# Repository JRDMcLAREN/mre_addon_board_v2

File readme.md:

# mre_addon_board_v2

Addon board for microrusEFI ECU.
Wideband controller wiring is based on https://github.com/mck1117/wideband, official rusEFI wideband controller.
This is a version using STM32F072C8Tx or STM32F072CBTx MCU in LQFP48 package.
(STM32F042C6T6 is not recommended for future release)

This addon board has build-in rusEFI wideband controller, microSD card slot and K-Thermocouple controller.
It can be used on all MREs with appropriate connector headers.

Wideband controller requires:
* CAN bus connectivity 
* additional power supply from 12V_MREL pin for sensor heater.
(not required for "my" MRE versions - R0.5.5rc, R0.6.1rc)

~~LSU 4.9 sensor wires are connected via MOLEX MicroFit 3x2 connector 43045-0601 or 43045-0612
K-Thermocouple wires are connected via MOLEX MicroFit 2x1 connector 43045-0202 or 43045-0212~~

Latest version use 2x4 pin connector MOLEX 43045-0800 or 43045-0812 (6pins for LSU and 2pins for K-Thermocouple).

Two analog outputs for external gauages are in progress.

SPI ChipSelect CS# pins:
PA15 - for EGT chip
PB9 - for microSD card

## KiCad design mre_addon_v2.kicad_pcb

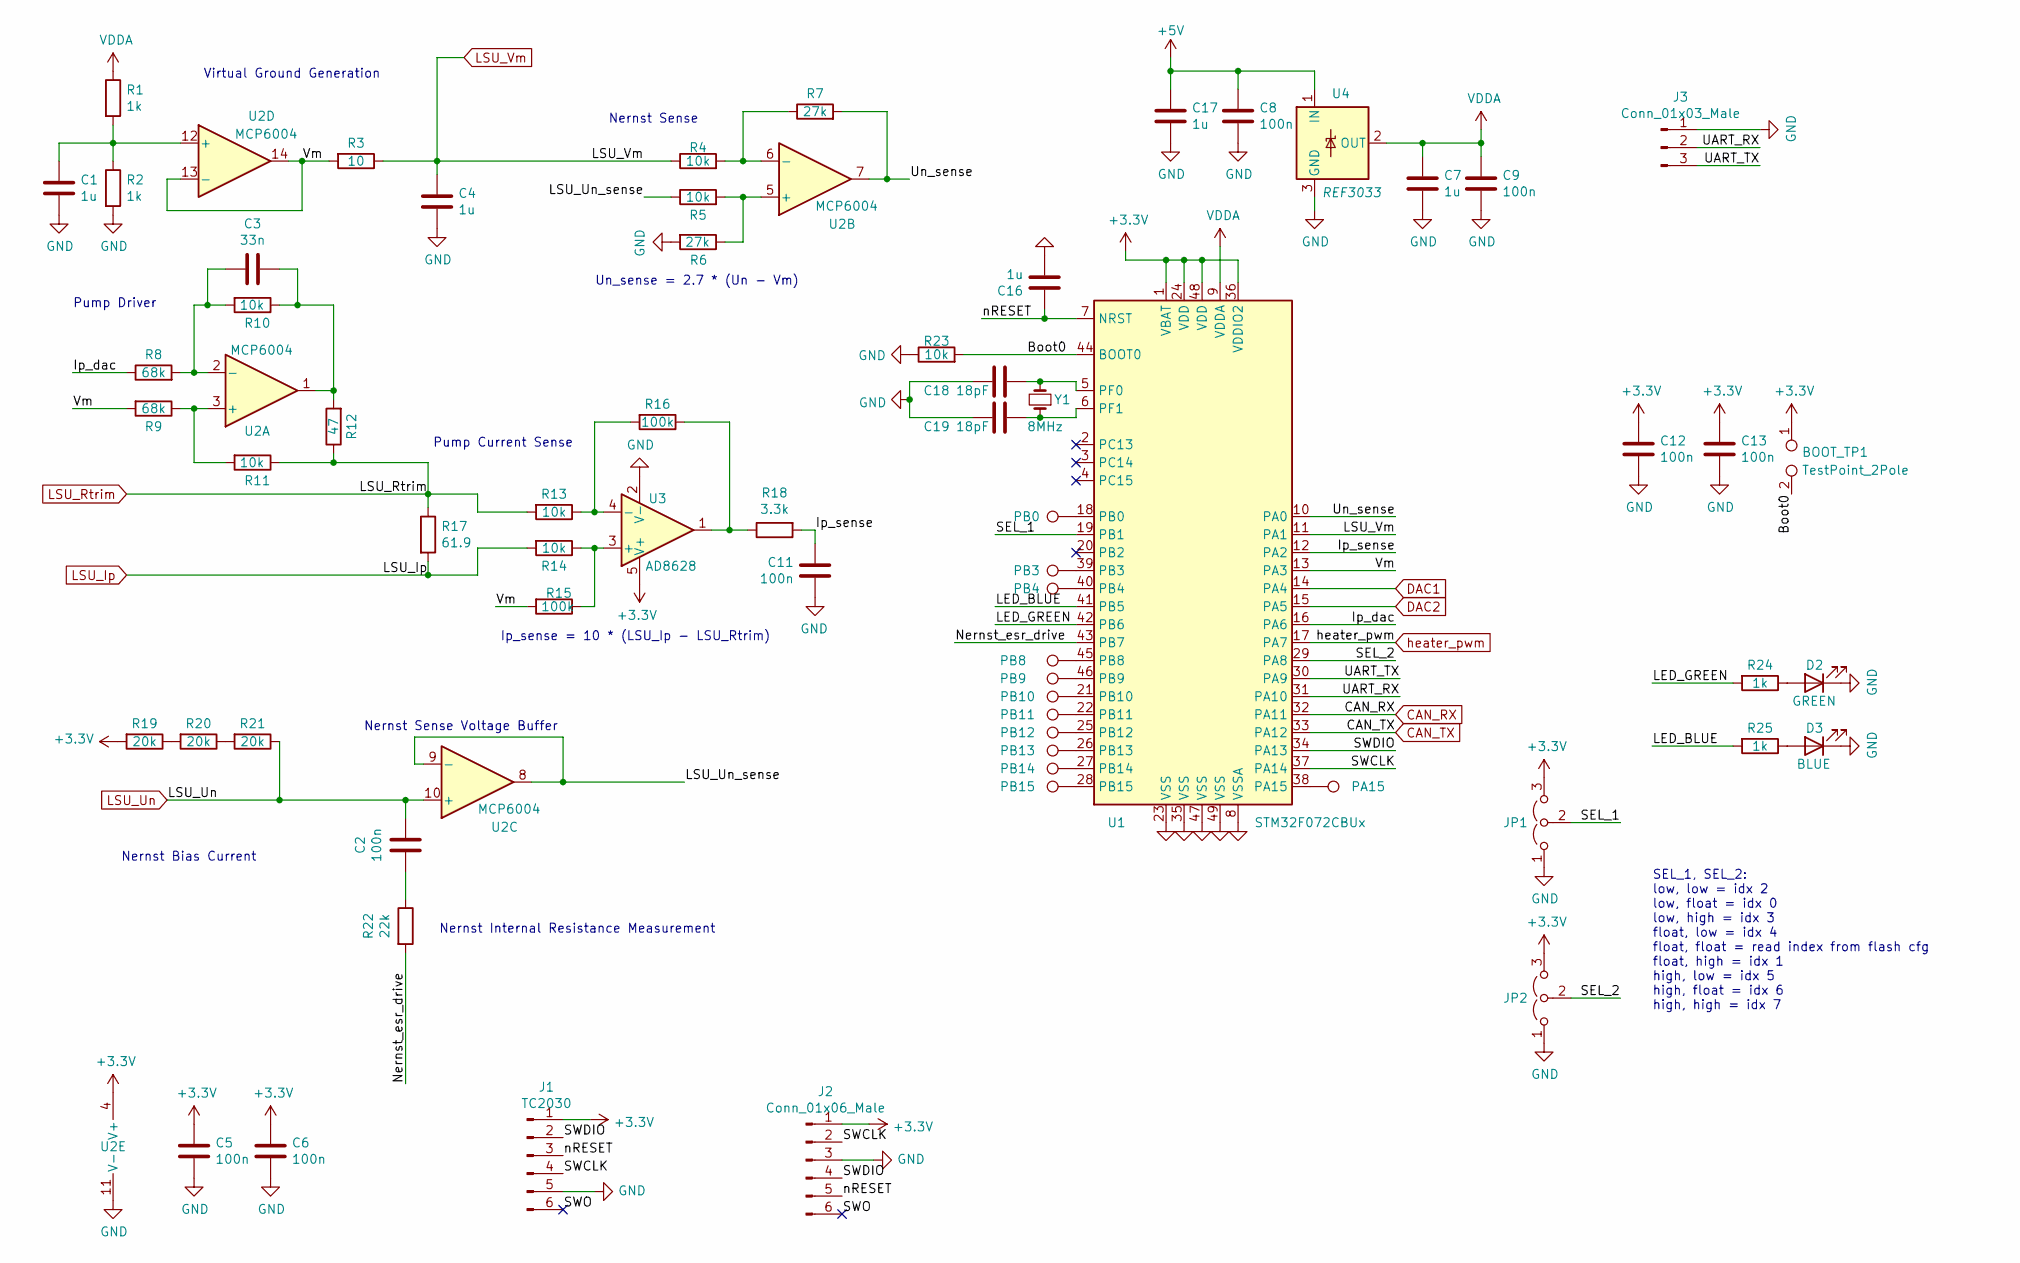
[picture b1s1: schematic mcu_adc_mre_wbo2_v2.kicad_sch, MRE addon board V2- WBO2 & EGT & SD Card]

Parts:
BOOT_TP1: TestPoint_2Pole; TestPoint_Bridge_Pitch2.54mm_Drill0.7mm
C1, C4, C7, C16, C17: 1u; C_0603_1608Metric; LCSC C52923
C2, C5, C6, C9, C11, C12, C13: 100n; C_0603_1608Metric; LCSC C1525
C3: 33n; C_0603_1608Metric; LCSC C1585
C8: 100n; C_0603_1608Metric
C18, C19: 18pF; C_0603_1608Metric
D2: GREEN; LED_0603_1608Metric; LCSC C72043
D3: BLUE; LED_0603_1608Metric; LCSC C72041
J1: TC2030; Tag-Connect_TC2030-IDC-NL_2x03_P1.27mm_Vertical
J2: Conn_01x06_Male; PinHeader_1x06_P2.54mm_Vertical
J3: Conn_01x03_Male; PinHeader_1x03_P2.54mm_Vertical
JP1, JP2: Jumper_3_Open; SolderJumper-3_P1.3mm_Open_Pad1.0x1.5mm
PA15: TestPoint; TestPoint_Pad_D1.0mm
PB0, PB3, PB4, PB8, PB9, PB10, PB11, PB12, PB13, PB14, PB15: TestPoint; TestPoint_Pad_D1.0mm
R1, R2, R24, R25: 1k; R_0603_1608Metric; LCSC C11702
R3: 10; R_0603_1608Metric; LCSC C25077
R4, R5, R10, R11, R13, R14, R23: 10k; R_0603_1608Metric; LCSC C25744
R6, R7: 27k; R_0603_1608Metric; LCSC C25771
R8, R9: 68k; R_0603_1608Metric; LCSC C36871
R12: 47; R_0603_1608Metric; LCSC C25118
R15, R16: 100k; R_0603_1608Metric; LCSC C25741
R17: 61.9; R_0603_1608Metric; LCSC C23092
R18: 3.3k; R_0603_1608Metric; LCSC C25890
R19, R20, R21: 20k; R_0603_1608Metric; LCSC C25765
R22: 22k; R_0603_1608Metric; LCSC C25768
U1: STM32F072CBUx; LQFP-48_7x7mm_P0.5mm
U2: MCP6004; TSSOP-14_4.4x5mm_P0.65mm; LCSC C50282
U3: AD8628; TSOT-23-5; LCSC C29309
U4: REF3033; SOT-23; LCSC C36658
Y1: 8MHz; Crystal_SMD_5032-2Pin_5.0x3.2mm

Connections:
+3.3V: BOOT_TP1.1, C5.1, C6.1, C12.1, C13.1, J1.1, J2.1, JP1.3 (B), JP2.3 (B), R19.2, U1.1 (VBAT), U1.24 (VDD), U1.36 (VDDIO2), U1.48 (VDD), U2.4 (V+), U3.5 (V+); also elsewhere on the board
+5V: C8.1, C17.1, U4.1 (IN); also elsewhere on the board
/mcu_adc_mre_wbo2_v2/Boot0: BOOT_TP1.2, R23.2, U1.44 (BOOT0)
/mcu_adc_mre_wbo2_v2/Ip_dac: R8.1, U1.16 (PA6)
/mcu_adc_mre_wbo2_v2/Ip_sense: C11.1, R18.2, U1.12 (PA2)
/mcu_adc_mre_wbo2_v2/LED_BLUE: R25.2, U1.41 (PB5)
/mcu_adc_mre_wbo2_v2/LED_GREEN: R24.2, U1.42 (PB6)
/mcu_adc_mre_wbo2_v2/LSU_Un_sense: R5.1, U2.8, U2.9 (-)
/mcu_adc_mre_wbo2_v2/Nernst_esr_drive: R22.2, U1.43 (PB7)
/mcu_adc_mre_wbo2_v2/SEL_1: JP1.2 (C), U1.19 (PB1)
/mcu_adc_mre_wbo2_v2/SEL_2: JP2.2 (C), U1.29 (PA8)
/mcu_adc_mre_wbo2_v2/SWCLK: J1.4, J2.2, U1.37 (PA14); also elsewhere on the board
/mcu_adc_mre_wbo2_v2/SWDIO: J1.2, J2.4, U1.34 (PA13); also elsewhere on the board
/mcu_adc_mre_wbo2_v2/SWO: J1.6, J2.6; also elsewhere on the board
/mcu_adc_mre_wbo2_v2/UART_RX: J3.2, U1.31 (PA10)
/mcu_adc_mre_wbo2_v2/UART_TX: J3.3, U1.30 (PA9)
/mcu_adc_mre_wbo2_v2/Un_sense: R7.2, U1.10 (PA0), U2.7
/mcu_adc_mre_wbo2_v2/Vm: R3.2, R9.2, R15.2, U1.13 (PA3), U2.13 (-), U2.14
/mcu_adc_mre_wbo2_v2/nRESET: C16.1, J1.3, J2.5, U1.7 (NRST); also elsewhere on the board
CAN_RX: U1.32 (PA11); also elsewhere on the board
CAN_TX: U1.33 (PA12); also elsewhere on the board
DAC1: U1.14 (PA4); also elsewhere on the board
DAC2: U1.15 (PA5); also elsewhere on the board
GND: C1.2, C4.2, C5.2, C6.2, C7.2, C8.2, C9.2, C11.2, C12.2, C13.2, C16.2, C17.2, C18.1, C19.1, D2.1 (K), D3.1 (K), J1.5, J2.3, J3.1, JP1.1 (A), JP2.1 (A), R2.2, R6.2, R23.1, U1.8 (VSSA), U1.23 (VSS), U1.35 (VSS), U1.47 (VSS), U1.49 (VSS), U2.11 (V-), U3.2 (V-), U4.3 (GND); also elsewhere on the board
LSU_Ip: R14.2, R17.2; also elsewhere on the board
LSU_Rtrim: R11.1, R12.1, R13.2, R17.1; also elsewhere on the board
LSU_Un: C2.1, R21.1, U2.10 (+); also elsewhere on the board
LSU_Vm: C4.1, R3.1, R4.1, U1.11 (PA1); also elsewhere on the board
unnamed: C1.1, R1.2, R2.1, U2.12 (+)
unnamed: C2.2, R22.1
unnamed: C3.1, R10.1, R12.2, U2.1
unnamed: C3.2, R8.2, R10.2, U2.2 (-)
unnamed: C18.2, U1.5 (PF0), Y1.2
unnamed: C19.2, U1.6 (PF1), Y1.1
unnamed 54: D2.2 (A), R24.1; also elsewhere on the board
unnamed 55: D3.2 (A), R25.1; also elsewhere on the board
unnamed: PA15.1, U1.38 (PA15)
unnamed: PB0.1, U1.18 (PB0)
unnamed: PB3.1, U1.39 (PB3)
unnamed: PB4.1, U1.40 (PB4)
unnamed: PB8.1, U1.45 (PB8)
unnamed: PB9.1, U1.46 (PB9)
unnamed: PB10.1, U1.21 (PB10)
unnamed: PB11.1, U1.22 (PB11)
unnamed: PB12.1, U1.25 (PB12)
unnamed: PB13.1, U1.26 (PB13)
unnamed: PB14.1, U1.27 (PB14)
unnamed: PB15.1, U1.28 (PB15)
unnamed: R4.2, R7.1, U2.6 (-)
unnamed: R5.2, R6.1, U2.5 (+)
unnamed: R9.1, R11.2, U2.3 (+)
unnamed 72: R13.1, R16.2, U3.4 (-); also elsewhere on the board
unnamed 73: R14.1, R15.1, U3.3 (+); also elsewhere on the board
unnamed 74: R16.1, R18.1, U3.1; also elsewhere on the board
unnamed: R19.1, R20.2
unnamed: R20.1, R21.2
VDDA: C7.1, C9.1, R1.1, U1.9 (VDDA), U4.2 (OUT)
heater_pwm: U1.17 (PA7); also elsewhere on the board

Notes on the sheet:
Un_sense = 2.7 * (Un - Vm)
Virtual Ground Generation
Pump Current Sense
Pump Driver
Ip_sense = 10 * (LSU_Ip - LSU_Rtrim)
Nernst Sense
Nernst Internal Resistance Measurement
Nernst Sense Voltage Buffer
SEL_1, SEL_2: low, low = idx 2 low, float = idx 0 low, high = idx 3 float, low = idx 4 float, float = read index from flash cfg float, high = idx 1 high, low = idx 5 high, float = idx 6 high, high = idx 7
Nernst Bias Current

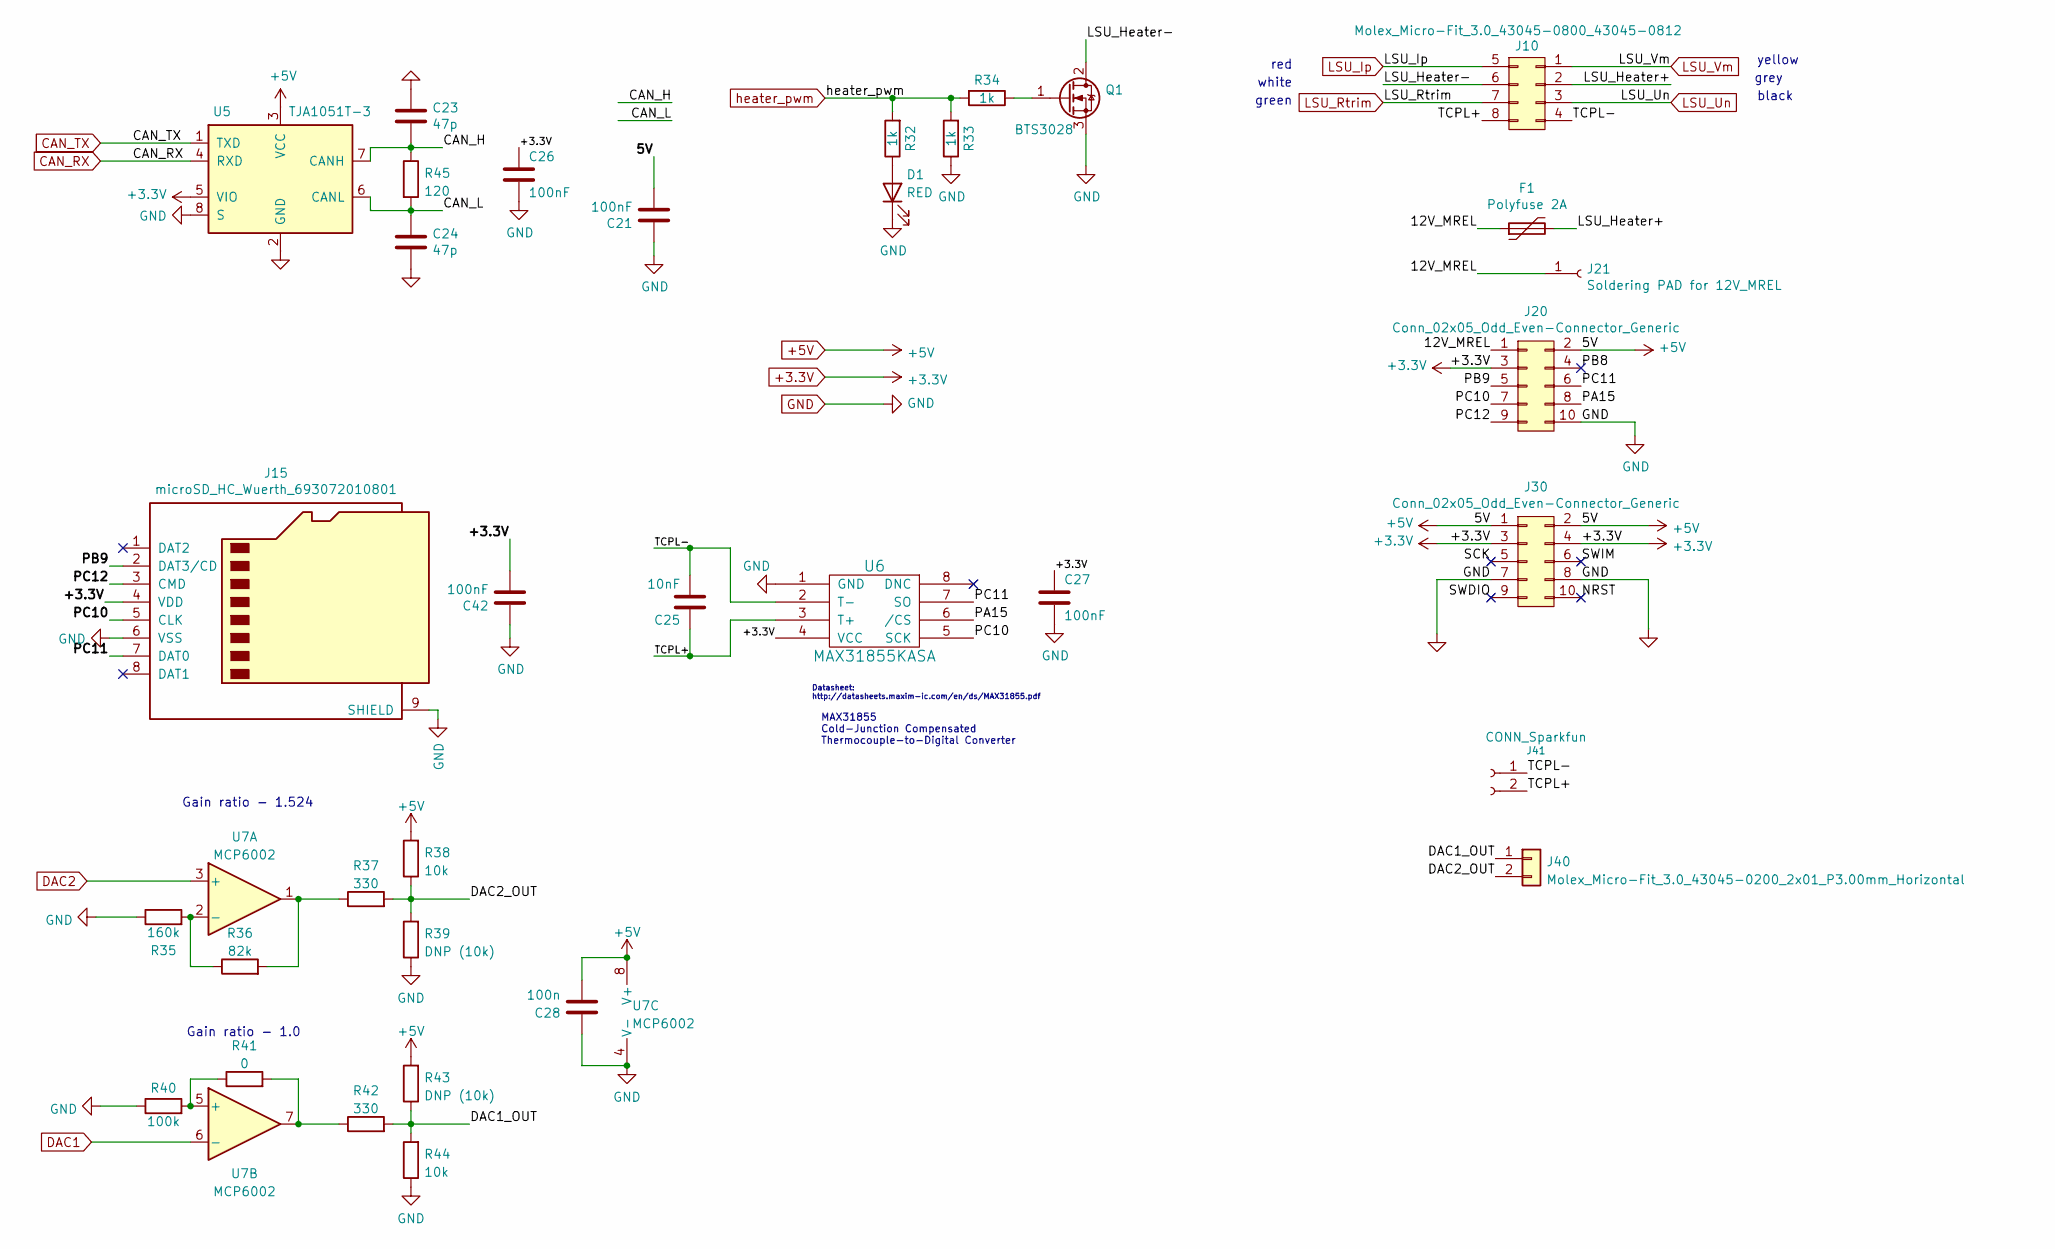
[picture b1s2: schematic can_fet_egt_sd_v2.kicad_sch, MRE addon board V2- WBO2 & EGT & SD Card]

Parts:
C21, C42: 100nF; C_0603_1608Metric; Part # C0603C104J5RACTU; LCSC C14663
C23, C24: 47p; C_0603_1608Metric; LCSC C1567
C25: 10nF; C_0603_1608Metric
C26, C27: 100nF; C_0603_1608Metric
C28: 100n; C_0603_1608Metric
D1: RED; LED_0603_1608Metric; LCSC C2286
F1: Polyfuse 2A; R_2816_7142Metric
J10: Molex_Micro-Fit_3.0_43045-0800_43045-0812; Molex_Micro-Fit_3.0_43045-0800_2x04_P3.00mm_Horizontal
J15: microSD_HC_Wuerth_693072010801; LCSC N/A
J20, J30: Conn_02x05_Odd_Even-Connector_Generic; PinHeader_2x05_P2.54mm_Vertical_SMD
J21: Soldering PAD for 12V_MREL; PinHeader_1x01_P2.54mm_Vertical
J40: Molex_Micro-Fit_3.0_43045-0200_2x01_P3.00mm_Horiz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; Molex_Micro-Fit_3.0_43045-0200_2x01_P3.00mm_Horizontal
J41: CONN_Sparkfun; tcpl_PCC-SMP
Q1: BTS3028; TO-252-2; LCSC C112639
R32, R33, R34: 1k; R_0603_1608Metric; LCSC C11702
R35: 160k; R_0603_1608Metric
R36: 82k; R_0603_1608Metric
R37, R42: 330; R_0603_1608Metric
R38, R44: 10k; R_0603_1608Metric
R39, R43: DNP (10k); R_0603_1608Metric
R40: 100k; R_0603_1608Metric
R41: 0; R_0603_1608Metric
R45: 120; R_0805_2012Metric
U5: TJA1051T-3; SOIC-8_3.9x4.9mm_P1.27mm; LCSC C38695
U6: MAX31855KASA; SOIC-8_3.9x4.9mm_P1.27mm
U7: MCP6002; SOIC-8_3.9x4.9mm_P1.27mm

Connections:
+3.3V: C26.1, C27.1, C42.2, J15.4 (VDD), J20.3, J30.3, J30.4, U5.5 (VIO), U6.4 (VCC); also elsewhere on the board
+5V: C21.2, C28.2, J20.2, J30.1, J30.2, R38.2, R43.2, U5.3 (VCC), U7.8 (V+); also elsewhere on the board
/can_fet_egt_sd_v2/12V_MREL: F1.1, J20.1, J21.1; also elsewhere on the board
/can_fet_egt_sd_v2/CAN_H: C23.2, R45.1, U5.7 (CANH); also elsewhere on the board
/can_fet_egt_sd_v2/CAN_L: C24.1, R45.2, U5.6 (CANL); also elsewhere on the board
/can_fet_egt_sd_v2/DAC1_OUT: J40.1, R42.2, R43.1, R44.2; also elsewhere on the board
/can_fet_egt_sd_v2/DAC2_OUT: J40.2, R37.2, R38.1, R39.2; also elsewhere on the board
/can_fet_egt_sd_v2/LSU_Heater+: F1.2, J10.2; also elsewhere on the board
/can_fet_egt_sd_v2/LSU_Heater-: J10.6, Q1.2 (D); also elsewhere on the board
/can_fet_egt_sd_v2/NRST: J30.10; also elsewhere on the board
/can_fet_egt_sd_v2/PA15: J20.8, U6.6 (/CS); also elsewhere on the board
/can_fet_egt_sd_v2/PB8: J20.4; also elsewhere on the board
/can_fet_egt_sd_v2/PB9: J15.2 (DAT3/CD), J20.5; also elsewhere on the board
/can_fet_egt_sd_v2/PC10: J15.5 (CLK), J20.7, U6.5 (SCK); also elsewhere on the board
/can_fet_egt_sd_v2/PC11: J15.7 (DAT0), J20.6, U6.7 (SO); also elsewhere on the board
/can_fet_egt_sd_v2/PC12: J15.3 (CMD), J20.9; also elsewhere on the board
/can_fet_egt_sd_v2/SCK: J30.5; also elsewhere on the board
/can_fet_egt_sd_v2/SWDIO: J30.9; also elsewhere on the board
/can_fet_egt_sd_v2/SWIM: J30.6; also elsewhere on the board
/can_fet_egt_sd_v2/TCPL+: C25.1, J10.8, J41.2, U6.3 (T+); also elsewhere on the board
/can_fet_egt_sd_v2/TCPL-: C25.2, J10.4, J41.1, U6.2 (T-); also elsewhere on the board
CAN_RX: U5.4 (RXD); also elsewhere on the board
CAN_TX: U5.1 (TXD); also elsewhere on the board
DAC1: U7.6 (-); also elsewhere on the board
DAC2: U7.3 (+); also elsewhere on the board
GND: C21.1, C23.1, C24.2, C26.2, C27.2, C28.1, C42.1, D1.1 (K), J15.6 (VSS), J15.9 (SHIELD), J20.10, J30.7, J30.8, Q1.3 (S), R33.1, R35.1, R39.1, R40.1, R44.1, U5.2 (GND), U5.8 (S), U6.1 (GND), U7.4 (V-); also elsewhere on the board
LSU_Ip: J10.5; also elsewhere on the board
LSU_Rtrim: J10.7; also elsewhere on the board
LSU_Un: J10.3; also elsewhere on the board
LSU_Vm: J10.1; also elsewhere on the board
unnamed 53: D1.2 (A), R32.1; also elsewhere on the board
unnamed: Q1.1 (G), R34.1
unnamed: R35.2, R36.1, U7.2 (-)
unnamed: R36.2, R37.1, U7.1
unnamed: R40.2, R41.1, U7.5 (+)
unnamed: R41.2, R42.1, U7.7
heater_pwm: R32.2, R33.2, R34.2; also elsewhere on the board

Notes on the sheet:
MAX31855 Cold-Junction Compensated Thermocouple-to-Digital Converter
white
Gain ratio - 1.524
Gain ratio - 1.0
green
grey
red
black
Datasheet: http://datasheets.maxim-ic.com/en/ds/MAX31855.pdf
yellow

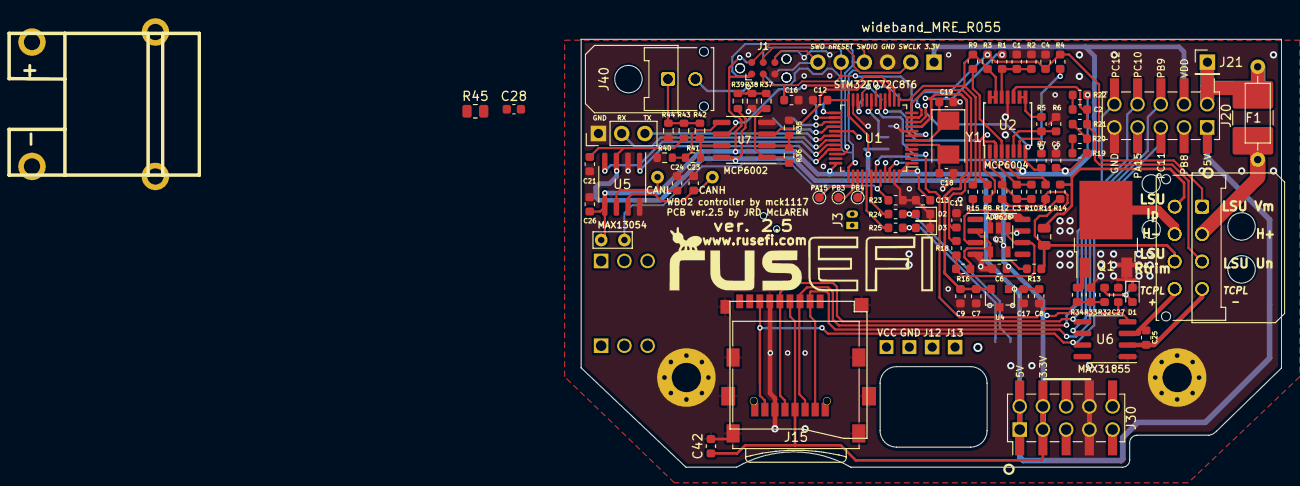
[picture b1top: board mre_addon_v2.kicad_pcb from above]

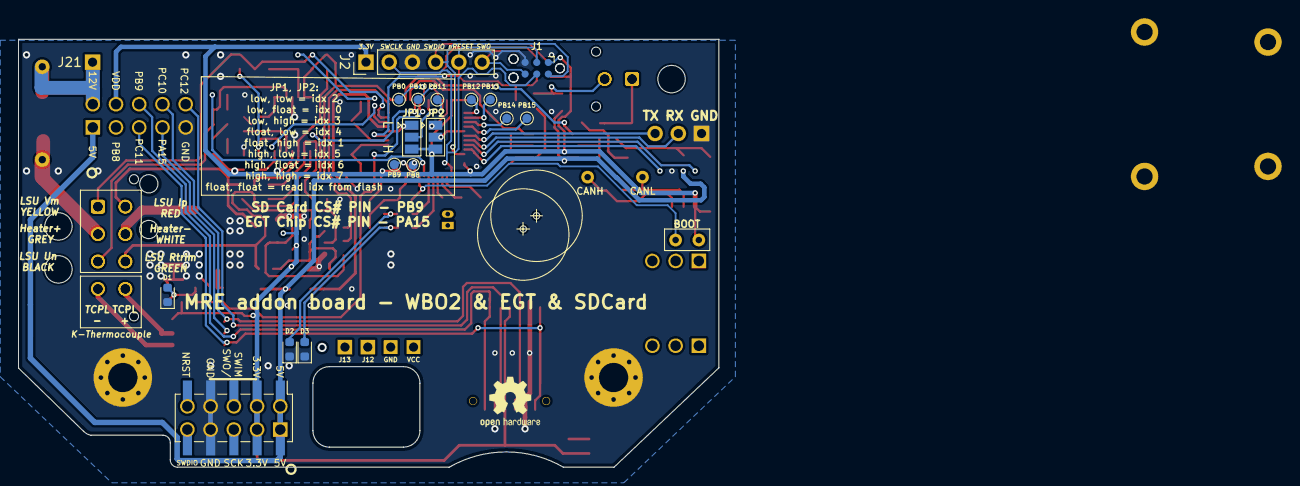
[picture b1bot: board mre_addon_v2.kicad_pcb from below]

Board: 2 copper layers, 76.6 x 46.8 mm, 116 parts (19 on the bottom side), 83 nets.

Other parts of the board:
D1#2: RED; LED_0603_1608Metric
D2#2: GREEN; LED_0603_1608Metric
D3#2: BLUE; LED_0603_1608Metric
F1#2: Polyfuse 2A; R_Axial_DIN0207_L6.3mm_D2.5mm_P10.16mm_Horizontal
G1: LOGO; mre_logo
H1, H2: MountingHole_3.2mm_M3_Pad_Via
J1#2: TC2030; Tag-Connect_TC2030-IDC-NL_2x03_P1.27mm_Vertical
J10#2: Molex_Micro-Fit_3.0_43045-0800_43045-0812; Molex_Micro-Fit_3.0_43045-0812_2x04_P3.00mm_Vertical
J15x: MICRO-SDCARD-CONNECTOR-3300060P1
J30x: Conn_02x05_Odd_Even-Connector_Generic; PinHeader_2x05_P2.54mm_Vertical_SMD
J40#2: Molex_Micro-Fit_3.0_43045-0200_2x01_P3.00mm_Horiz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; Molex_Micro-Fit_3.0_43045-0200_2x01_P3.00mm_Horizontal
LOGO1: DNP; OSHW-Logo2_7.3x6mm_SilkScreen
U0: wideband_MRE_R055
U3x: SO-8_3.9x4.9mm_P1.27mm

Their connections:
+3.3V: J1#2.1, J15x.4, J30x.3, J30x.4, U0.J203, U0.J204, U0.J804, U3x.7; also elsewhere on the board
+5V: J30x.1, J30x.2, U0.J201, U0.J202, U0.J801; also elsewhere on the board
/can_fet_egt_sd_v2/12V_MREL: F1#2.1, U0.J802; also elsewhere on the board
/can_fet_egt_sd_v2/CAN_H: U0.J49; also elsewhere on the board
/can_fet_egt_sd_v2/CAN_L: U0.J50; also elsewhere on the board
/can_fet_egt_sd_v2/DAC1_OUT: J40#2.1; also elsewhere on the board
/can_fet_egt_sd_v2/DAC2_OUT: J40#2.2; also elsewhere on the board
/can_fet_egt_sd_v2/LSU_Heater+: F1#2.2, J10#2.2; also elsewhere on the board
/can_fet_egt_sd_v2/LSU_Heater-: J10#2.6; also elsewhere on the board
/can_fet_egt_sd_v2/NRST: J30x.9, U0.J210; also elsewhere on the board
/can_fet_egt_sd_v2/PA15: U0.J807; also elsewhere on the board
/can_fet_egt_sd_v2/PB8: U0.J803; also elsewhere on the board
/can_fet_egt_sd_v2/PB9: J15x.2, U0.J806; also elsewhere on the board
/can_fet_egt_sd_v2/PC10: J15x.5, U0.J808; also elsewhere on the board
/can_fet_egt_sd_v2/PC11: J15x.7, U0.J805; also elsewhere on the board
/can_fet_egt_sd_v2/PC12: J15x.3, U0.J810; also elsewhere on the board
/can_fet_egt_sd_v2/SCK: J30x.6, U0.J205; also elsewhere on the board
/can_fet_egt_sd_v2/SWDIO: J30x.10, U0.J209; also elsewhere on the board
/can_fet_egt_sd_v2/SWIM: J30x.5, U0.J206; also elsewhere on the board
/can_fet_egt_sd_v2/TCPL+: J10#2.8; also elsewhere on the board
/can_fet_egt_sd_v2/TCPL-: J10#2.4; also elsewhere on the board
/mcu_adc_mre_wbo2_v2/SWCLK: J1#2.4; also elsewhere on the board
/mcu_adc_mre_wbo2_v2/SWDIO: J1#2.2; also elsewhere on the board
/mcu_adc_mre_wbo2_v2/SWO: J1#2.6; also elsewhere on the board
/mcu_adc_mre_wbo2_v2/nRESET: J1#2.3; also elsewhere on the board
GND: D1#2.1 (K), D2#2.1 (K), D3#2.1 (K), H1.1, H2.1, J1#2.5, J15x.6, J15x.G1, J15x.G2, J15x.G3, J15x.G4, J30x.7, J30x.8, U0.J207, U0.J208, U0.J809, U3x.4, U3x.8; also elsewhere on the board
LSU_Ip: J10#2.5; also elsewhere on the board
LSU_Rtrim: J10#2.7; also elsewhere on the board
LSU_Un: J10#2.3; also elsewhere on the board
LSU_Vm: J10#2.1; also elsewhere on the board
unnamed 53: D1#2.2 (A); also elsewhere on the board
unnamed 54: D2#2.2 (A); also elsewhere on the board
unnamed 55: D3#2.2 (A); also elsewhere on the board
unnamed 72: U3x.2; also elsewhere on the board
unnamed 73: U3x.3; also elsewhere on the board
unnamed 74: U3x.6; also elsewhere on the board

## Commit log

2023-01-19 ver2.5 in progress
2023-01-26 V2.5 with OPAmp
2023-01-26 BOM ver2.3
2023-01-26 PIC of V2.3
2023-01-26 PIC of v2.2
2023-02-04 tried to improve wording
    I'm not sure to have understood original description for " MRE versions pre R0.5.5rc" correctly!
    Please edit or comment in case I had wrong understanding
2023-02-05 some changes on DAC pins
2023-02-13 V2.5 - 13.02.2023
